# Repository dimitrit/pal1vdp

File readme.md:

# PAL-1 Sprite Colour Graphics Adapter

The PAL-1 Sprite Colour Graphics Adapter is an expansion board for the PAL-1 system<sup>1</sup>, 
based on the Texas Instruments TMS9918A Video Display Processor (VDP)<sup>2</sup> and was inspired 
by a Ciarcia's Circuit Cellar project<sup>3</sup>. 

The TMS9918A VDP was used in video systems to provide data display on raster scanned colour
television sets or monitors. The IC generates all necessary video, control, and synchronisation
signals and also controls the storage and retrieval of display data in its own dedicated screen 
memory. 

> **Note**  
> The TMS9918A VDP generates a 525-line NTSC encoded colour video signal. While the TMS9928A
> VDP, which is intended for use with PAL video systems, is functionally compatible with the
> TMS9918A, it is not pin-for-pin compatible. Thus it is **not possible** to use the TMS9928A 
> VDP in the PAL-1 Sprite Colour Graphics Adapter. Instead, users who do not have access to an 
> NTSC TV or monitor are recommended to use AV to HDMI or AV to VGA converters as appropriate.
> Such converters are widely available from the usual e-commerce and auction web sites. 

## Acknowledgements
The SRAM circuitry is based on work by Tom LeMense and Dan Werner<sup>4,5</sup>.  
PAL-1 and the PAL-1 logo used with kind permission of Liu Ganning.

## References
1. Liu Ganning, ‘PAL-1 Microcomputer User Manual’, 2020 <http://pal.aibs.ws/assets/PAL_en.pdf> [accessed 21 July 2022].
2. ‘9900 TMS9918A/TMS9928A/TMS9929A Video Display Processors’ (Texas Instruments Incorporated, 1982) <https://web.archive.org/web/20180717212934/https://emu-docs.org/VDP%20TMS9918/Datasheets/TMS9918.pdf> [accessed 17 September 2022].
3. Steve Ciarcia, ‘High-Resolution Sprite-Oriented Color Graphics’, Byte, 7.8 (1982), 57–80.
4. Tom LeMense, ‘SRAM Replacement for TMS99x8 VRAM’, 2010 <https://retrobrewcomputers.org/n8vem-pbwiki-archive/0/35845334/48860720/33053543/SRAM%20Replacement%20for%20TMS99x8%20VRAM.pdf> [accessed 17 September 2022].
5. Tom LeMense and Dan Werner, ‘Video Display Interface Board’, RetroBrew Computers Wiki, 2021 <https://www.retrobrewcomputers.org/doku.php?id=boards:ecb:scg:start> [accessed 17 September 2022].

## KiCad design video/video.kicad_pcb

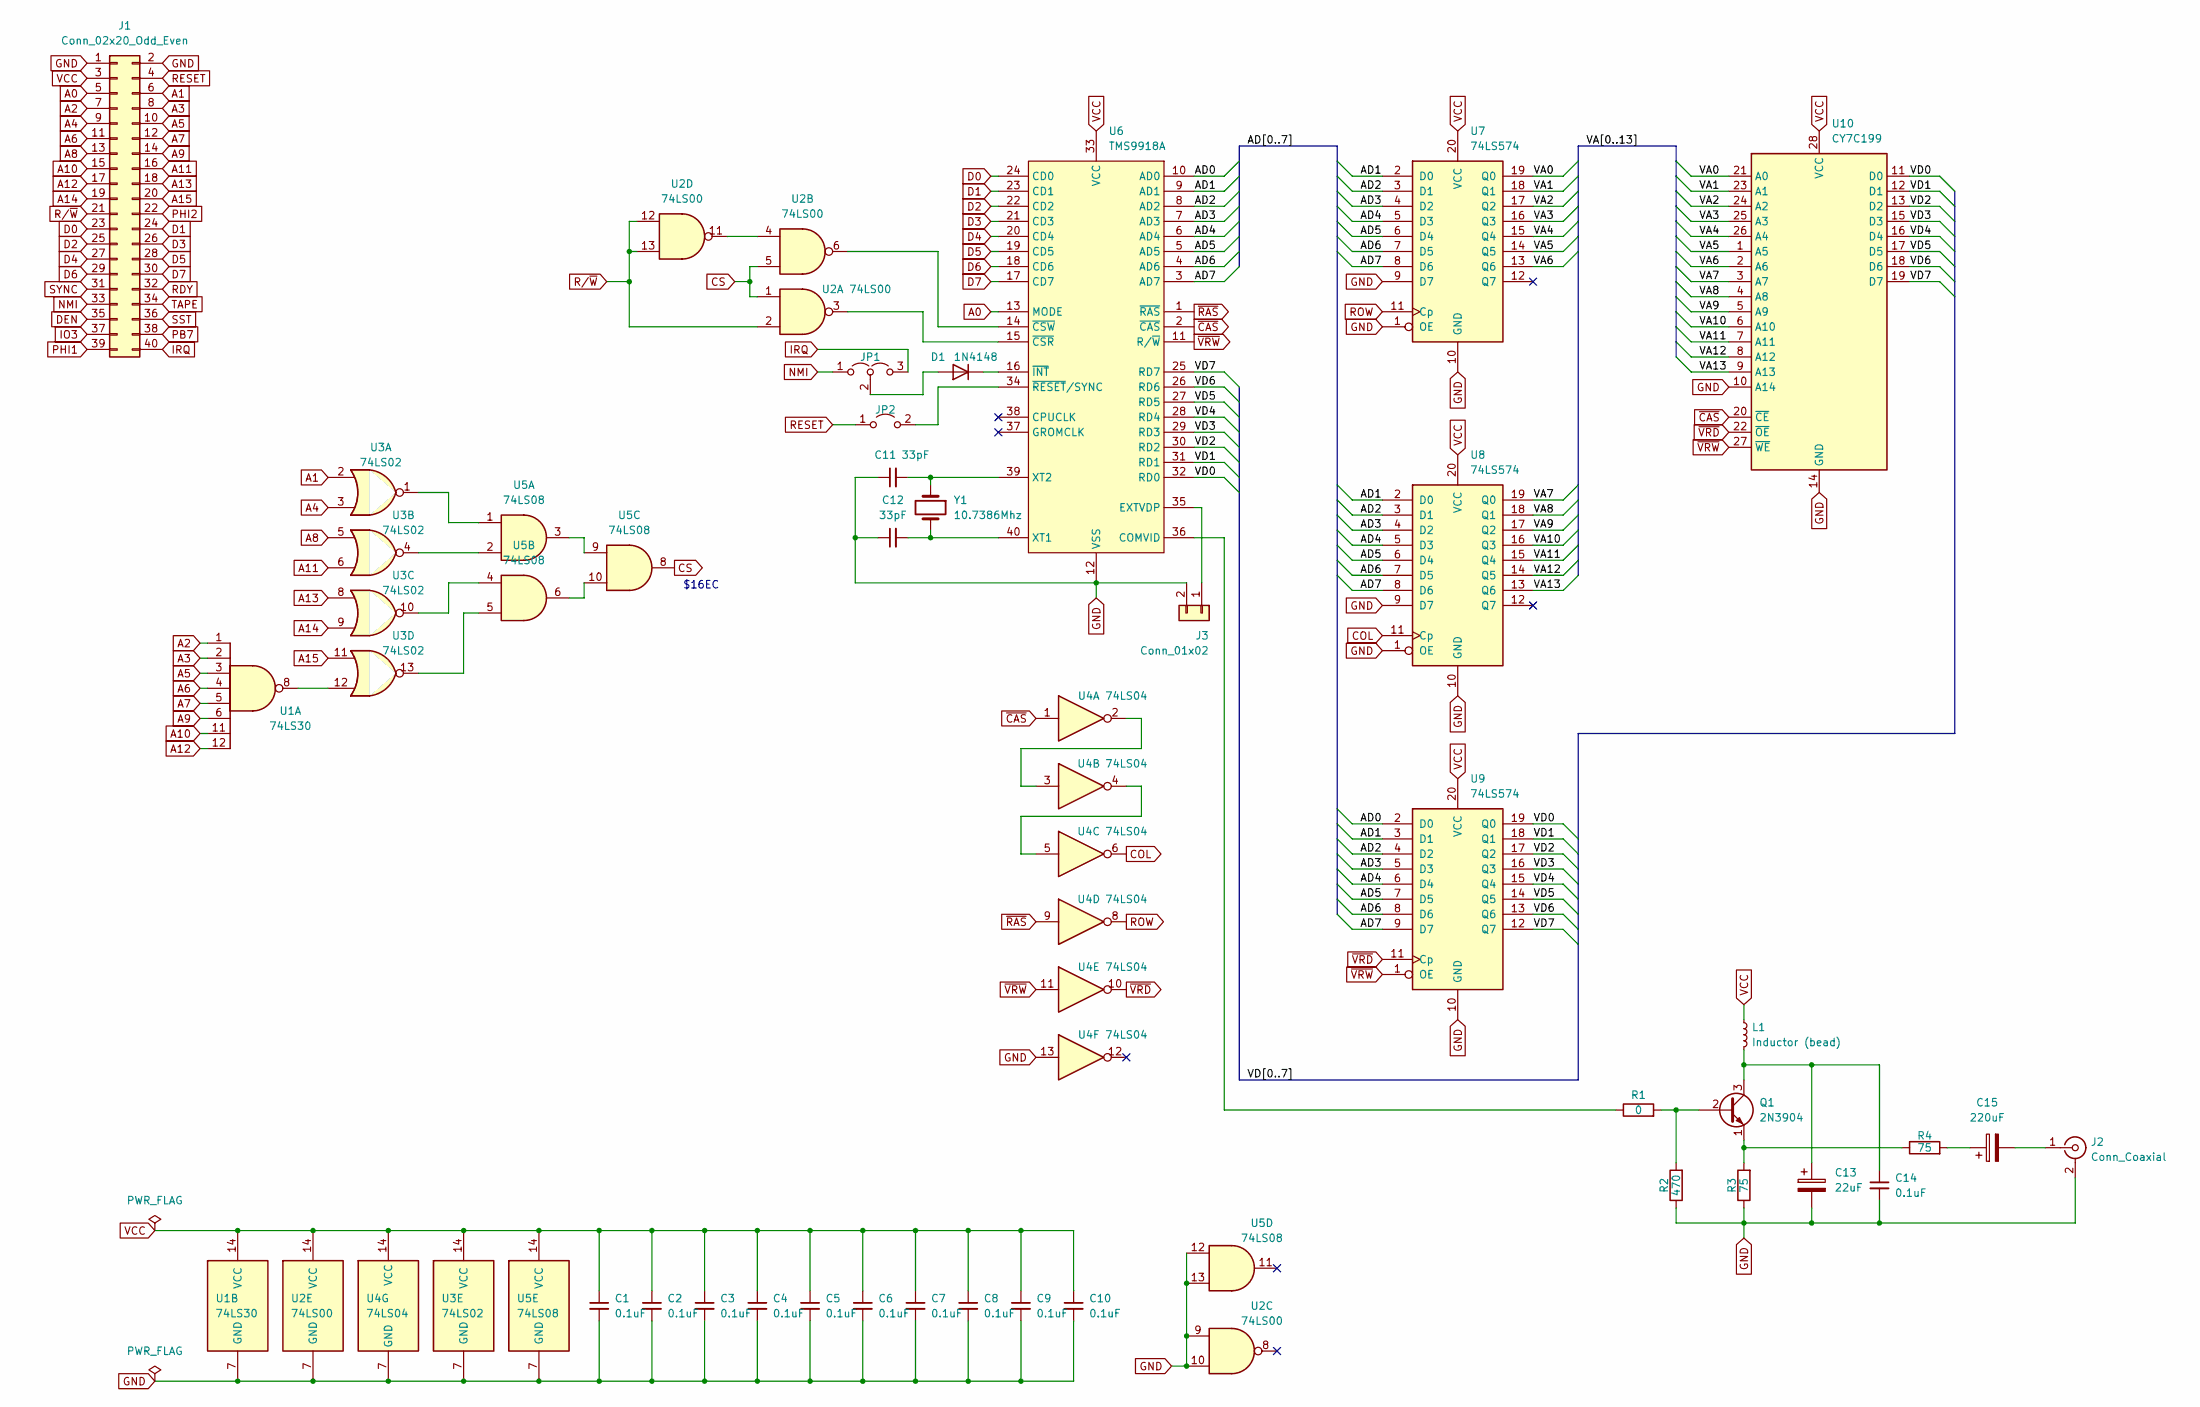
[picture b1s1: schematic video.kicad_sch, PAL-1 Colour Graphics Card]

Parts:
C1, C2, C3, C4, C5, C6, C7, C8, C9, C10, C14: 0.1uF; C_Disc_D3.0mm_W1.6mm_P2.50mm
C11, C12: 33pF; C_Disc_D4.7mm_W2.5mm_P5.00mm
C13: 22uF; CP_Radial_D5.0mm_P2.50mm
C15: 220uF; CP_Radial_D5.0mm_P2.50mm
D1: 1N4148; D_DO-35_SOD27_P7.62mm_Horizontal
J1: Conn_02x20_Odd_Even; PinHeader_2x20_P2.54mm_Vertical
J2: Conn_Coaxial; RCA right angle phono
J3: Conn_01x02; PinHeader_1x02_P2.54mm_Vertical
JP1: Jumper_3_Open; PinHeader_1x03_P2.54mm_Vertical
JP2: Jumper_2_Open; PinHeader_1x02_P2.54mm_Vertical
L1: Inductor (bead); L_Axial_L7.0mm_D3.3mm_P10.16mm_Horizontal_Fastron_MICC
Q1: 2N3904; TO-92_Inline
R1: 0; R_Axial_DIN0207_L6.3mm_D2.5mm_P7.62mm_Horizontal
R2: 470; R_Axial_DIN0207_L6.3mm_D2.5mm_P7.62mm_Horizontal
R3, R4: 75; R_Axial_DIN0207_L6.3mm_D2.5mm_P7.62mm_Horizontal
U1: 74LS30; DIP-14_W7.62mm
U2: 74LS00; DIP-14_W7.62mm
U3: 74LS02; DIP-14_W7.62mm
U4: 74LS04; DIP-14_W7.62mm
U5: 74LS08; DIP-14_W7.62mm
U6: TMS9918A; DIP-40_W15.24mm
U7, U8, U9: 74LS574; DIP-20_W7.62mm
U10: CY7C199; DIP-28_W7.62mm
Y1: 10.7386Mhz; Crystal_HC49-U_Vertical

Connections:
/AD0: U6.10 (AD0), U9.2 (D0)
/AD1: U6.9 (AD1), U7.2 (D0), U8.2 (D0), U9.3 (D1)
/AD2: U6.8 (AD2), U7.3 (D1), U8.3 (D1), U9.4 (D2)
/AD3: U6.7 (AD3), U7.4 (D2), U8.4 (D2), U9.5 (D3)
/AD4: U6.6 (AD4), U7.5 (D3), U8.5 (D3), U9.6 (D4)
/AD5: U6.5 (AD5), U7.6 (D4), U8.6 (D4), U9.7 (D5)
/AD6: U6.4 (AD6), U7.7 (D5), U8.7 (D5), U9.8 (D6)
/AD7: U6.3 (AD7), U7.8 (D6), U8.8 (D6), U9.9 (D7)
/VA0: U7.19 (Q0), U10.21 (A0)
/VA1: U7.18 (Q1), U10.23 (A1)
/VA2: U7.17 (Q2), U10.24 (A2)
/VA3: U7.16 (Q3), U10.25 (A3)
/VA4: U7.15 (Q4), U10.26 (A4)
/VA5: U7.14 (Q5), U10.1 (A5)
/VA6: U7.13 (Q6), U10.2 (A6)
/VA7: U8.19 (Q0), U10.3 (A7)
/VA8: U8.18 (Q1), U10.4 (A8)
/VA9: U8.17 (Q2), U10.5 (A9)
/VA10: U8.16 (Q3), U10.6 (A10)
/VA11: U8.15 (Q4), U10.7 (A11)
/VA12: U8.14 (Q5), U10.8 (A12)
/VA13: U8.13 (Q6), U10.9 (A13)
/VD0: U6.32 (RD0), U9.19 (Q0), U10.11 (D0)
/VD1: U6.31 (RD1), U9.18 (Q1), U10.12 (D1)
/VD2: U6.30 (RD2), U9.17 (Q2), U10.13 (D2)
/VD3: U6.29 (RD3), U9.16 (Q3), U10.15 (D3)
/VD4: U6.28 (RD4), U9.15 (Q4), U10.16 (D4)
/VD5: U6.27 (RD5), U9.14 (Q5), U10.17 (D5)
/VD6: U6.26 (RD6), U9.13 (Q6), U10.18 (D6)
/VD7: U6.25 (RD7), U9.12 (Q7), U10.19 (D7)
A0: J1.5, U6.13 (MODE)
A1: J1.6, U3.2
A2: J1.7, U1.1
A3: J1.8, U1.2
A4: J1.9, U3.3
A5: J1.10, U1.3
A6: J1.11, U1.4
A7: J1.12, U1.5
A8: J1.13, U3.5
A9: J1.14, U1.6
A10: J1.15, U1.11
A11: J1.16, U3.6
A12: J1.17, U1.12
A13: J1.18, U3.8
A14: J1.19, U3.9
A15: J1.20, U3.11
COL: U4.6, U8.11 (Cp)
CS: U2.1, U2.5, U5.8
D0: J1.23, U6.24 (CD0)
D1: J1.24, U6.23 (CD1)
D2: J1.25, U6.22 (CD2)
D3: J1.26, U6.21 (CD3)
D4: J1.27, U6.20 (CD4)
D5: J1.28, U6.19 (CD5)
D6: J1.29, U6.18 (CD6)
D7: J1.30, U6.17 (CD7)
DEN: J1.35
GND: C1.2, C2.2, C3.2, C4.2, C5.2, C6.2, C7.2, C8.2, C9.2, C10.2, C11.1, C12.1, C13.2, C14.2, J1.1, J1.2, J2.2 (Ext), J3.2, R2.1, R3.1, U1.7 (GND), U2.7 (GND), U2.9, U2.10, U3.7 (GND), U4.7 (GND), U4.13, U5.7 (GND), U5.12, U5.13, U6.12 (VSS), U7.1 (OE), U7.9 (D7), U7.10 (GND), U8.1 (OE), U8.9 (D7), U8.10 (GND), U9.10 (GND), U10.10 (A14), U10.14 (GND)
IO3: J1.37
IRQ: J1.40, JP1.3 (B)
NMI: J1.33, JP1.1 (A)
unnamed: C11.2, U6.39 (XT2), Y1.1
unnamed: C12.2, U6.40 (XT1), Y1.2
unnamed: C13.1, C14.1, L1.2, Q1.3 (C)
unnamed: C15.1, R4.2
unnamed: C15.2, J2.1 (In)
unnamed: D1.1 (K), U6.16 (~INT)
unnamed: D1.2 (A), JP1.2 (C)
unnamed: J3.1, U6.35 (EXTVDP)
unnamed: JP2.2 (B), U6.34 (~RESET/SYNC)
unnamed: Q1.1 (E), R3.2, R4.1
unnamed: Q1.2 (B), R1.2, R2.2
unnamed: R1.1, U6.36 (COMVID)
unnamed: U1.8, U3.12
unnamed: U2.3, U6.15 (~CSR)
unnamed: U2.6, U6.14 (~CSW)
unnamed: U2.4, U2.11
unnamed: U3.1, U5.1
unnamed: U3.4, U5.2
unnamed: U3.10, U5.4
unnamed: U3.13, U5.5
unnamed: U4.2, U4.3
unnamed: U4.4, U4.5
unnamed: U5.3, U5.9
unnamed: U5.6, U5.10
PB7: J1.38
PHI1: J1.39
PHI2: J1.22
RDY: J1.32
RESET: J1.4, JP2.1 (A)
ROW: U4.8, U7.11 (Cp)
R/~W: J1.21, U2.2, U2.12, U2.13
SST: J1.36
SYNC: J1.31
TAPE: J1.34
VCC: C1.1, C2.1, C3.1, C4.1, C5.1, C6.1, C7.1, C8.1, C9.1, C10.1, J1.3, L1.1, U1.14 (VCC), U2.14 (VCC), U3.14 (VCC), U4.14 (VCC), U5.14 (VCC), U6.33 (VCC), U7.20 (VCC), U8.20 (VCC), U9.20 (VCC), U10.28 (VCC)
~CAS: U4.1, U6.2 (~CAS), U10.20 (~CE)
~RAS: U4.9, U6.1 (~RAS)
~VRD: U4.10, U9.11 (Cp), U10.22 (~OE)
~VRW: U4.11, U6.11 (R/~W), U9.1 (OE), U10.27 (~WE)

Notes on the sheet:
$16EC

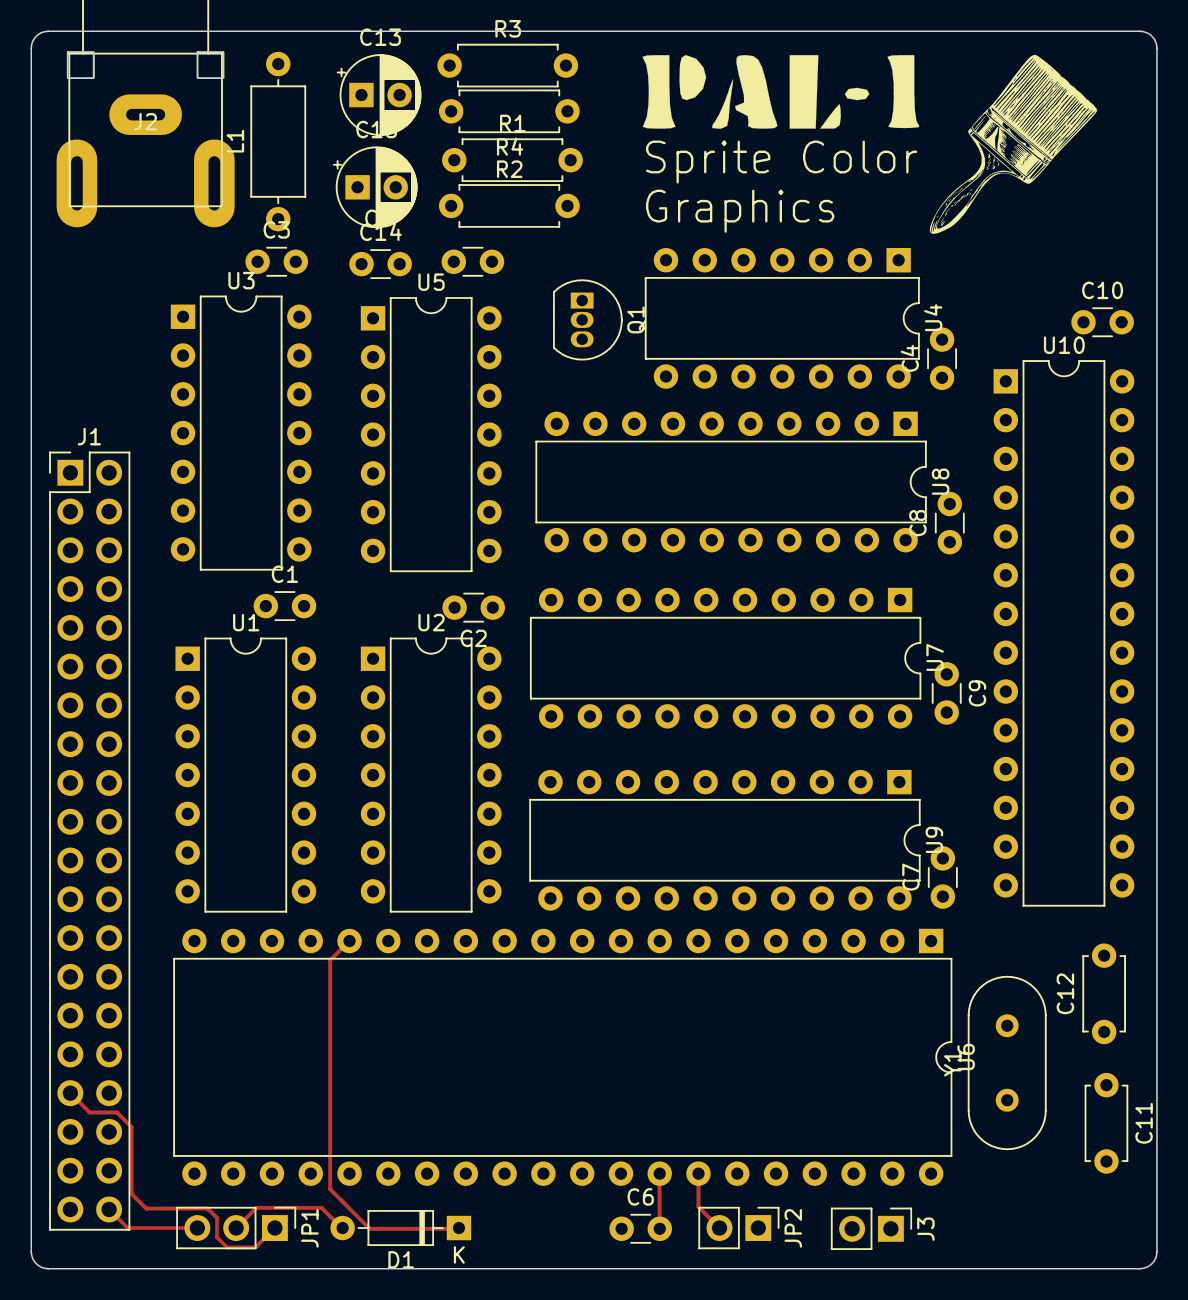
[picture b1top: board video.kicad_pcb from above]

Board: 2 copper layers, 73.7 x 81.1 mm, 38 parts (0 on the bottom side), 90 nets.

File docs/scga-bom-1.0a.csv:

Ref;Qnty;Value;Description
C1 -- C10, C13;11;0.1uF;Unpolarized capacitor
C11, C12;2;33pF;Unpolarized capacitor
C14;1;22uF;Polarized capacitor
C15;1;220uF;Polarized capacitor
J1;1;Connector;Generic connector, double row, 02x20
J2;1;EXTVDP;Generic connector, double row, 02x05
J3;1;RCA;RCA jack
JP1;1;/RST;Jumper, 3-pole
JP2;1;/IRQ;Jumper, 2-pole
JP3;1;ADDRESS;Jumper, 3-pole
L1;1;Inductor;Inductor, small bead
Q1;1;2N3904;Small Signal NPN Transistor, TO-92
R1, R2;2;4K7;Resistor, 250mA
R3;1;0;Resistor, 250mA
R4;1;470;Resistor, 250mA
R5, R6;2;75;Resistor, 250mA
U1;1;74LS30;8-input NAND
U2;1;74LS00;Quad 2-input NAND
U3;1;74LS02;Quad 2-input NOR
U4;1;74LS04;Hex Inverter
U5;1;74LS08;Quad 2-input AND
U6;1;TMS9918A;Video Display Processor
U7, U8, U9;3;74LS574;8-bit Register
U10;1;CY7C199;Static RAM, 32K x 8
Y1;1;10.7386Mhz;Two pin crystal

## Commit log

2022-09-17 Update documentation
2022-09-21 Initial version of schema
2022-10-06 Initial pcb layout
2024-08-23 Add images
2024-08-23 Add code example
2024-08-23 Add documentation
2024-08-23 Update appendixes
2024-08-23 Update component descriptions
